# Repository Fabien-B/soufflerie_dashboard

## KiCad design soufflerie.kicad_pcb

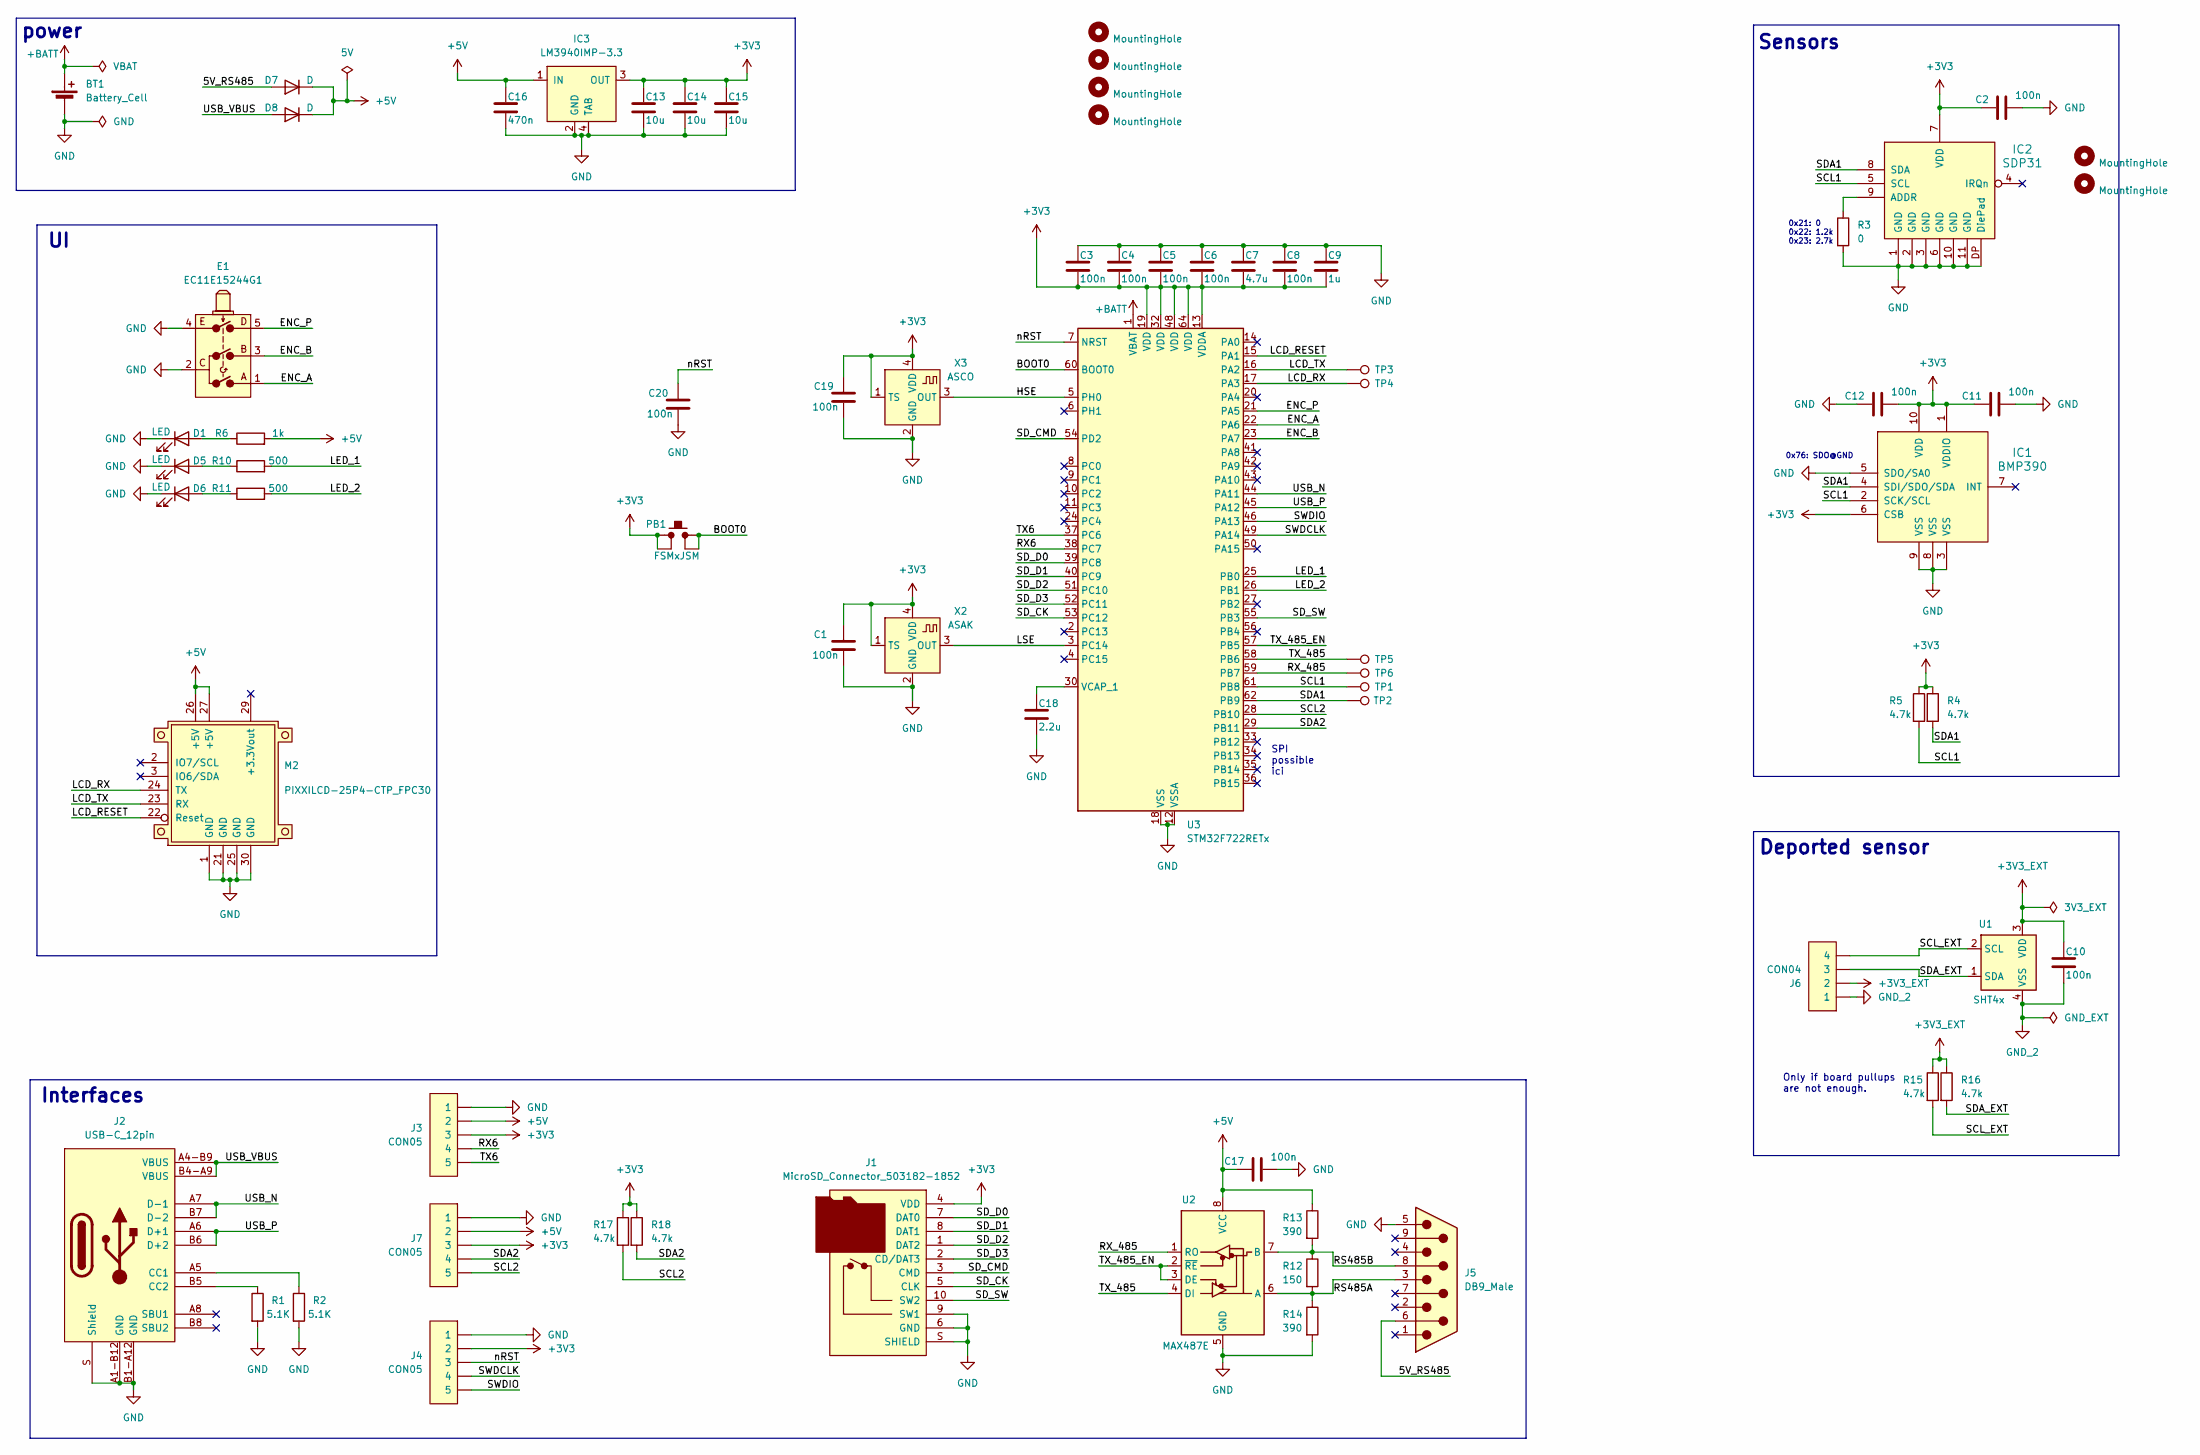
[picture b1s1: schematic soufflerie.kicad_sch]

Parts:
BT1: Battery_Cell; BatteryHolder_Keystone_3000_1x12mm
C1, C2, C3, C4, C5, C6, C8, C10, C11, C12, C17, C19, C20: 100n; C_0603_1608Metric
C7: 4.7u; C_0603_1608Metric
C9: 1u; C_0603_1608Metric
C13, C14, C15: 10u; C_0603_1608Metric
C16: 470n; C_0603_1608Metric
C18: 2.2u; C_0603_1608Metric
D1, D5, D6: LED; LED_0603_1608Metric
D7, D8: D; PMEG2010EB
E1: EC11E15244G1
H1, H2, H3, H4: MountingHole; MountingHole_3.2mm_M3
H5, H6: MountingHole; MountingHole_2.2mm_M2
IC1: BMP390
IC2: SDP31
IC3: LM3940IMP-3.3; LM3940IMP
J1: MicroSD_Connector_503182-1852; MicroSD_503182-1852
J2: USB-C_12pin; USB-C_HRO_C-31-M-12
J3, J4, J7: CON05; PicoBlade_53398-0571
J5: DB9_Male; DSUB-9_Male_Horizontal_P2.77x2.84mm_EdgePinOffset7.70mm_Hou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
J6: CON04; PicoBlade_53398-0471
M2: PIXXILCD-25P4-CTP_FPC30
PB1: FSMxJSM; FSM2JSM
R1, R2: 5.1K; R_0603_1608Metric
R3: 0; R_0603_1608Metric
R4, R5, R15, R16, R17, R18: 4.7k; R_0603_1608Metric
R6: 1k; R_0603_1608Metric
R10, R11: 500; R_0603_1608Metric
R12: 150; R_0603_1608Metric
R13, R14: 390; R_0603_1608Metric
TP1, TP2, TP3, TP4, TP5, TP6: TestPoint; TestPoint_Pad_D2.0mm
U1: SHT4x; Sensirion_DFN-4_1.5x1.5mm_P0.8mm_SHT4x_NoCentralPad
U2: MAX487E; SOIC-8_3.9x4.9mm_P1.27mm
U3: STM32F722RETx; LQFP-64_10x10mm_P0.5mm
X2: ASAK; Osc_ASAK
X3: ASCO; Osc_ASCO

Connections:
+3V3: C1.1, C2.1, C3.2, C4.2, C5.2, C6.2, C7.2, C8.2, C9.2, C11.1, C12.2, C13.1, C14.1, C15.1, C19.1, IC1.1 (VDDIO), IC1.6 (CSB), IC1.10 (VDD), IC2.7 (VDD), IC3.3 (OUT), J1.4 (VDD), J3.3, J4.2, J7.3, PB1.1, PB1.2, R4.1, R5.1, R17.1, R18.1, U3.13 (VDDA), U3.19 (VDD), U3.32 (VDD), U3.48 (VDD), U3.64 (VDD), X2.1 (TS), X2.4 (VDD), X3.1 (TS), X3.4 (VDD)
+3V3_EXT: C10.1, J6.2, R15.1, R16.1, U1.3 (VDD)
+5V: C16.1, C17.1, D7.1 (K), D8.1 (K), IC3.1 (IN), J3.2, J7.2, M2.26 (+5V), M2.27 (+5V), R6.2, R13.1, U2.8 (VCC)
+BATT: BT1.1 (+), U3.1 (VBAT)
/5V_RS485: D7.2 (A), J5.6
/BOOT0: PB1.3, PB1.4, U3.60 (BOOT0)
/ENC_A: E1.1, U3.22 (PA6)
/ENC_B: E1.3, U3.23 (PA7)
/ENC_P: E1.5, U3.21 (PA5)
/HSE: U3.5 (PH0), X3.3 (OUT)
/LCD_RESET: M2.22 (Reset), U3.15 (PA1)
/LCD_RX: M2.24 (TX), TP4.1, U3.17 (PA3)
/LCD_TX: M2.23 (RX), TP3.1, U3.16 (PA2)
/LED_1: R10.2, U3.25 (PB0)
/LED_2: R11.2, U3.26 (PB1)
/LSE: U3.3 (PC14), X2.3 (OUT)
/RS485A: J5.3, R12.2, R14.1, U2.6 (A)
/RS485B: J5.8, R12.1, R13.2, U2.7 (B)
/RX6: J3.4, U3.38 (PC7)
/RX_485: TP6.1, U2.1 (RO), U3.59 (PB7)
/SCL1: IC1.2 (SCK/SCL), IC2.5 (SCL), R5.2, TP1.1, U3.61 (PB8)
/SCL2: J7.5, R17.2, U3.28 (PB10)
/SCL_EXT: J6.4, R15.2, U1.2 (SCL)
/SDA1: IC1.4 (SDI/SDO/SDA), IC2.8 (SDA), R4.2, TP2.1, U3.62 (PB9)
/SDA2: J7.4, R18.2, U3.29 (PB11)
/SDA_EXT: J6.3, R16.2, U1.1 (SDA)
/SD_CK: J1.5 (CLK), U3.53 (PC12)
/SD_CMD: J1.3 (CMD), U3.54 (PD2)
/SD_D0: J1.7 (DAT0), U3.39 (PC8)
/SD_D1: J1.8 (DAT1), U3.40 (PC9)
/SD_D2: J1.1 (DAT2), U3.51 (PC10)
/SD_D3: J1.2 (CD/DAT3), U3.52 (PC11)
/SD_SW: J1.10 (SW2), U3.55 (PB3)
/SWDCLK: J4.4, U3.49 (PA14)
/SWDIO: J4.5, U3.46 (PA13)
/TX6: J3.5, U3.37 (PC6)
/TX_485: TP5.1, U2.4 (DI), U3.58 (PB6)
/TX_485_EN: U2.2 (~RE), U2.3 (DE), U3.57 (PB5)
/USB_N: J2.A7 (D-1), J2.B7 (D-2), U3.44 (PA11)
/USB_P: J2.A6 (D+1), J2.B6 (D+2), U3.45 (PA12)
/USB_VBUS: D8.2 (A), J2.A4-B9 (VBUS), J2.B4-A9 (VBUS)
/nRST: C20.1, J4.3, U3.7 (NRST)
GND: BT1.2 (-), C1.2, C2.2, C3.1, C4.1, C5.1, C6.1, C7.1, C8.1, C9.1, C11.2, C12.1, C13.2, C14.2, C15.2, C16.2, C17.2, C18.2, C19.2, C20.2, D1.1 (K), D5.1 (K), D6.1 (K), E1.2, E1.4, IC1.3 (VSS), IC1.5 (SDO/SA0), IC1.8 (VSS), IC1.9 (VSS), IC2.1 (GND), IC2.2 (GND), IC2.3 (GND), IC2.6 (GND), IC2.10 (GND), IC2.11 (GND), IC2.DP (DiePad), IC3.2 (GND), IC3.4 (TAB), J1.6 (GND), J1.9 (SW1), J1.S (SHIELD), J2.A1-B12 (GND), J2.B1-A12 (GND), J2.S (Shield), J3.1, J4.1, J5.5, J7.1, M2.1 (GND), M2.21 (GND), M2.25 (GND), M2.30 (GND), R1.2, R2.2, R3.2, R14.2, U2.5 (GND), U3.12 (VSSA), U3.18 (VSS), U3.31 (VSS), U3.47 (VSS), U3.63 (VSS), X2.2 (GND), X3.2 (GND)
GND_2: C10.2, J6.1, U1.4 (VSS)
unnamed: D1.2 (A), R6.1
unnamed: D5.2 (A), R10.1
unnamed: D6.2 (A), R11.1
unnamed: IC2.9 (ADDR), R3.1
unnamed: J2.A5 (CC1), R2.1
unnamed: J2.B5 (CC2), R1.1
unnamed: C18.1, U3.30 (VCAP_1)

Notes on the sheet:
Interfaces
Only if board pullups are not enough.
0x76: SDO@GND
SPI possible ici
0x21: 0 0x22: 1.2k 0x23: 2.7k
Sensors
Deported sensor
power

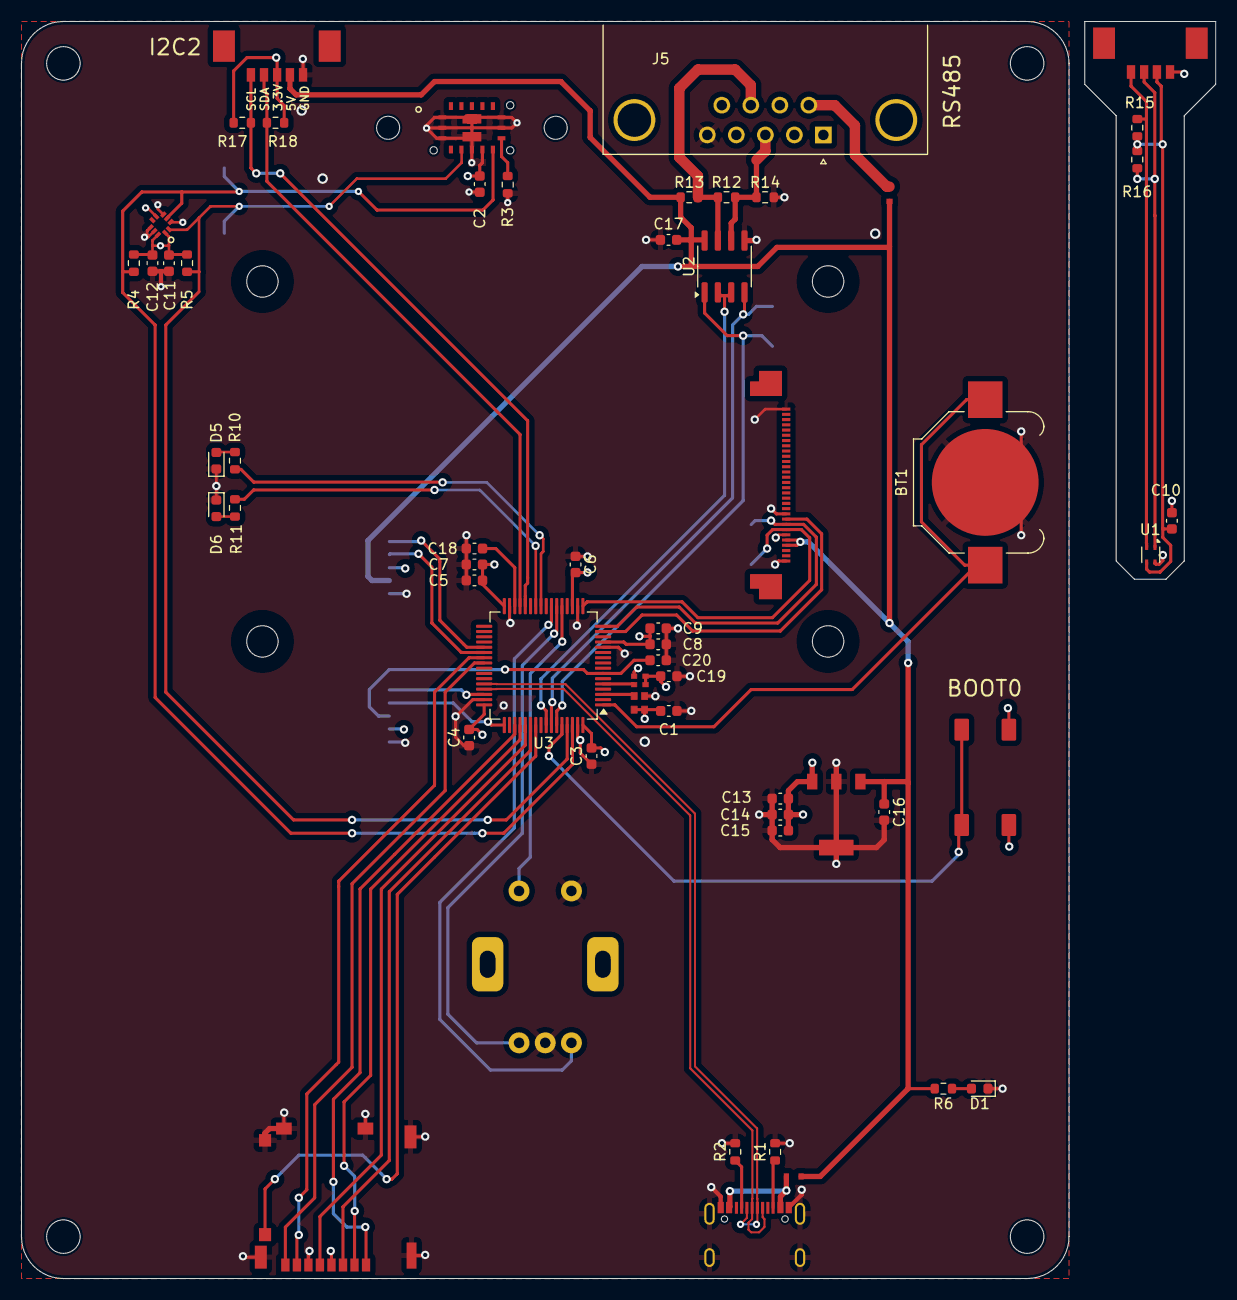
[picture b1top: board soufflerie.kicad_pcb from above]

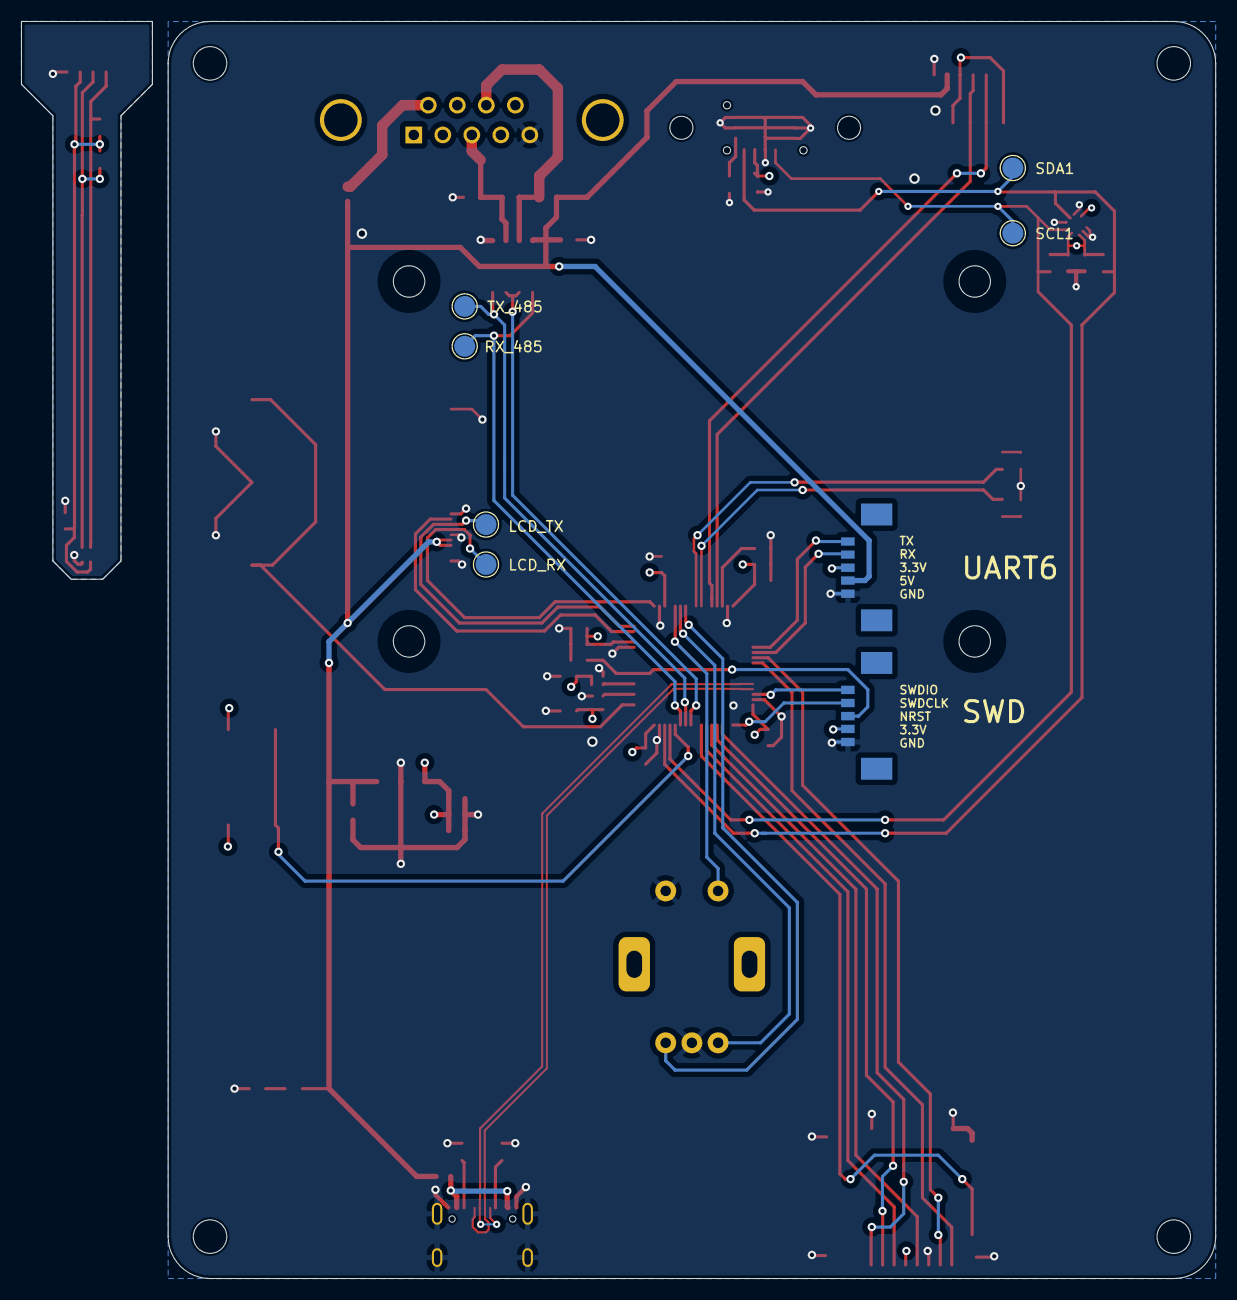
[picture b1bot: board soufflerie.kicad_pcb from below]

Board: 4 copper layers, 114.0 x 120.0 mm, 71 parts (8 on the bottom side), 51 nets.

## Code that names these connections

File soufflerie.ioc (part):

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Mcu.Name=STM32F722R(C-E)Tx
Mcu.Package=LQFP64
Mcu.UserName=STM32F722RETx
PA1.GPIOParameters=GPIO_Label
PA1.GPIO_Label=LCD_RESET
PA1.Signal=GPIO_Output
PA11.Mode=Device_Only
PA11.Signal=USB_OTG_FS_DM
PA12.Mode=Device_Only
PA12.Signal=USB_OTG_FS_DP
PA13.Mode=Serial_Wire
PA13.Signal=SYS_JTMS-SWDIO
PA14.Mode=Serial_Wire
PA14.Signal=SYS_JTCK-SWCLK
PA2.GPIOParameters=GPIO_Label
PA2.GPIO_Label=LCD_TX
PA2.Mode=Asynchronous
PA2.Signal=USART2_TX
PA3.GPIOParameters=GPIO_Label
PA3.GPIO_Label=LCD_RX
PA3.Mode=Asynchronous
PA3.Signal=USART2_RX
PA5.GPIOParameters=GPIO_Label
PA5.GPIO_Label=ENC_P
PA5.Signal=GPIO_Input
PA6.GPIOParameters=GPIO_Label
PA6.GPIO_Label=ENC_A
PA6.Signal=S_TIM3_CH1
PA7.GPIOParameters=GPIO_Label
PA7.GPIO_Label=ENC_B
PA7.Signal=S_TIM3_CH2
PB0.GPIOParameters=GPIO_Label
PB0.GPIO_Label=LED_1
PB0.Signal=GPIO_Output
PB1.GPIOParameters=GPIO_Label
PB1.GPIO_Label=LED_2
PB1.Signal=GPIO_Output
PB10.Mode=I2C
PB10.Signal=I2C2_SCL
PB11.Mode=I2C
PB11.Signal=I2C2_SDA
PB3.GPIOParameters=GPIO_Label
PB3.GPIO_Label=SD_SW
PB3.Signal=GPIO_Input
PB5.GPIOParameters=GPIO_Label
PB5.GPIO_Label=TX_485_EN
PB5.Signal=GPIO_Output
PB6.GPIOParameters=GPIO_Label
PB6.GPIO_Label=TX_485
PB6.Mode=Asynchronous
PB6.Signal=USART1_TX
PB7.GPIOParameters=GPIO_Label
PB7.GPIO_Label=RX_485
PB7.Mode=Asynchronous
PB7.Signal=USART1_RX
PB8.Mode=I2C
PB8.Signal=I2C1_SCL
PB9.Mode=I2C
PB9.Signal=I2C1_SDA
PC10.Mode=mmc_4_bits_Wide_bus
PC10.Signal=SDMMC1_D2
PC11.Mode=mmc_4_bits_Wide_bus
PC11.Signal=SDMMC1_D3
PC12.Mode=mmc_4_bits_Wide_bus
PC12.Signal=SDMMC1_CK
PC14-OSC32_IN.Mode=LSE-External-Clock-Source
PC14-OSC32_IN.Signal=RCC_OSC32_IN
PC15-OSC32_OUT.Mode=LSE-External-Clock-Source
PC15-OSC32_OUT.Signal=RCC_OSC32_OUT
PC2.GPIOParameters=GPIO_Label
PC2.GPIO_Label=LED_RS485
PC2.Signal=GPIO_Output
PC6.Mode=Asynchronous
PC6.Signal=USART6_TX
PC7.Mode=Asynchronous
PC7.Signal=USART6_RX
PC8.Mode=mmc_4_bits_Wide_bus
PC8.Signal=SDMMC1_D0
PC9.Mode=mmc_4_bits_Wide_bus
PC9.Signal=SDMMC1_D1
PD2.Mode=mmc_4_bits_Wide_bus
PD2.Signal=SDMMC1_CMD
PH0-OSC_IN.Mode=HSE-External-Clock-Source
PH0-OSC_IN.Signal=RCC_OSC_IN
PH1-OSC_OUT.Mode=HSE-External-Clock-Source
PH1-OSC_OUT.Signal=RCC_OSC_OUT
RCC.HSE_VALUE=8000000
RCC.SYSCLKFreq_VALUE=216000000
RCC.SYSCLKSource=RCC_SYSCLKSOURCE_PLLCLK
board=custom

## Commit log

2024-04-10 Add HSE oscillator
2024-04-10 select DB9 footprint
2024-04-10 routage
2024-04-11 silkscreen
2024-04-11 connect SDP31 DIE pad
2024-04-11 add sensor probe
2024-04-11 add a few vias
2024-04-11 fix unconnected pad.
2024-04-11 Panelize boards
2024-11-19 start firmware
2024-11-19 Read SDP31
2024-11-19 Add driver for SHT4x
2024-11-19 Display tunnel temperature.
2024-11-20 Add SD card support
2024-11-21 better display
2024-11-21 Start USS driver.
2024-11-21 [USS] Put drivers config in USSConfig.
2024-11-21 [USS] Use packed struct for telegram.
2024-11-21 [USS] move configs and drivers where they belong.
2024-11-21 [USS] stop uart receive on residual timeout.
2024-11-21 [USS] Add PWE AK definitions
2024-11-22 USS log
2024-11-22 remove traces
2024-11-27 sdLog
2024-11-29 Fix UART config
2024-12-02 USS Log and RS485 TX working
2024-12-02 better UI
